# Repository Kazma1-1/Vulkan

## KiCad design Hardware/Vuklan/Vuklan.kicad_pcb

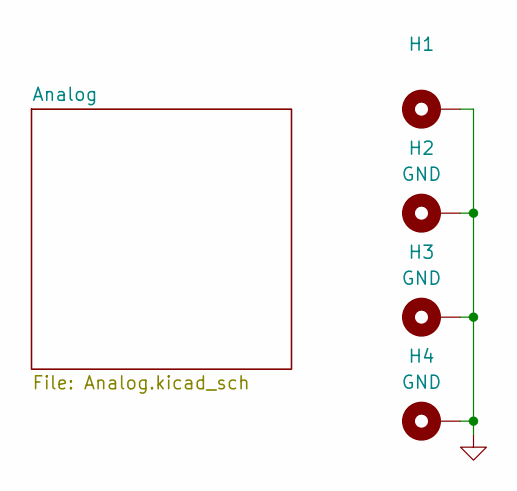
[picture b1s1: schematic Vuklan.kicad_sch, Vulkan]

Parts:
H1: (no value)
H2, H3, H4: GND

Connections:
GND: H1.1, H2.1, H3.1, H4.1; also elsewhere on the board

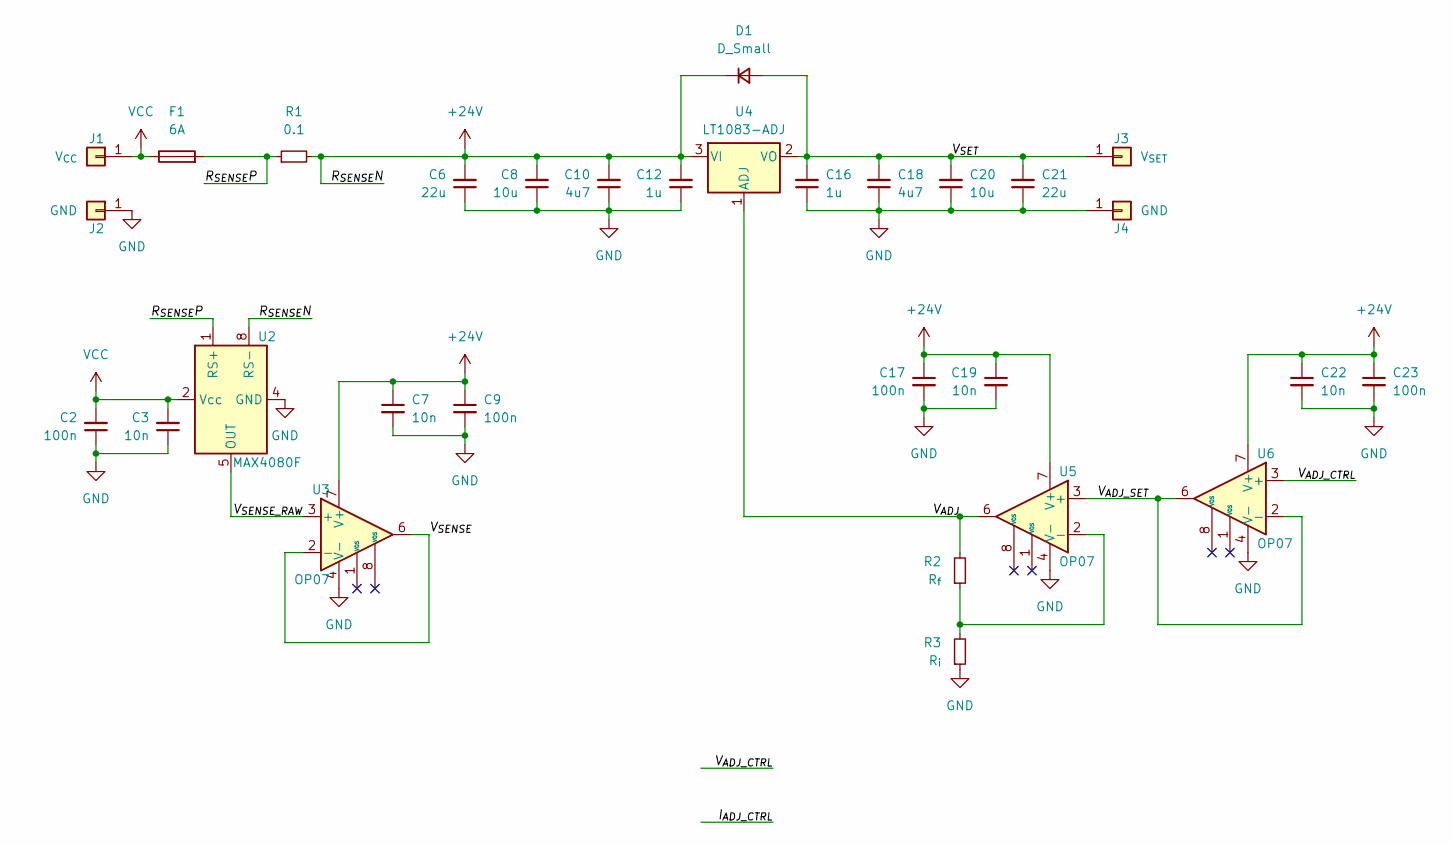
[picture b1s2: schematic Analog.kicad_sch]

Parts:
C2, C9, C17, C23: 100n
C3, C7, C19, C22: 10n
C6, C21: 22u
C8, C20: 10u
C10, C18: 4u7
C12, C16: 1u
D1: D_Small
F1: 6A
J1: V_{CC}
J2, J4: GND
J3: V_{SET}
R1: 0.1
R2: R_{f}
R3: R_{i}
U2: MAX4080F; SOIC-8_3.9x4.9mm_P1.27mm
U3, U5, U6: OP07
U4: LT1083-ADJ

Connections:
+24V: C6.2, C7.1, C8.2, C9.1, C10.2, C12.2, C17.1, C19.1, C22.1, C23.1, D1.1 (K), R1.2, U2.8 (RS-), U3.7 (V+), U4.3 (VI), U5.7 (V+), U6.7 (V+)
/Analog/R_{SENSE}P: F1.2, R1.1, U2.1 (RS+)
/Analog/V_{ADJ_CTRL}: U6.3 (+)
/Analog/V_{ADJ_SET}: U5.3 (+), U6.2 (-), U6.6
/Analog/V_{ADJ}: R2.2, U4.1 (ADJ), U5.6
/Analog/V_{SENSE_RAW}: U2.5 (OUT), U3.3 (+)
/Analog/V_{SENSE}: U3.2 (-), U3.6
/Analog/V_{SET}: C16.2, C18.2, C20.2, C21.2, D1.2 (A), J3.1, U4.2 (VO)
GND: C2.1, C3.1, C6.1, C7.2, C8.1, C9.2, C10.1, C12.1, C16.1, C17.2, C18.1, C19.2, C20.1, C21.1, C22.2, C23.2, J2.1, J4.1, R3.1, U2.4 (GND), U3.4 (V-), U5.4 (V-), U6.4 (V-); also elsewhere on the board
unnamed: R2.1, R3.2, U5.2 (-)
VCC: C2.2, C3.2, F1.1, J1.1, U2.2 (Vcc)

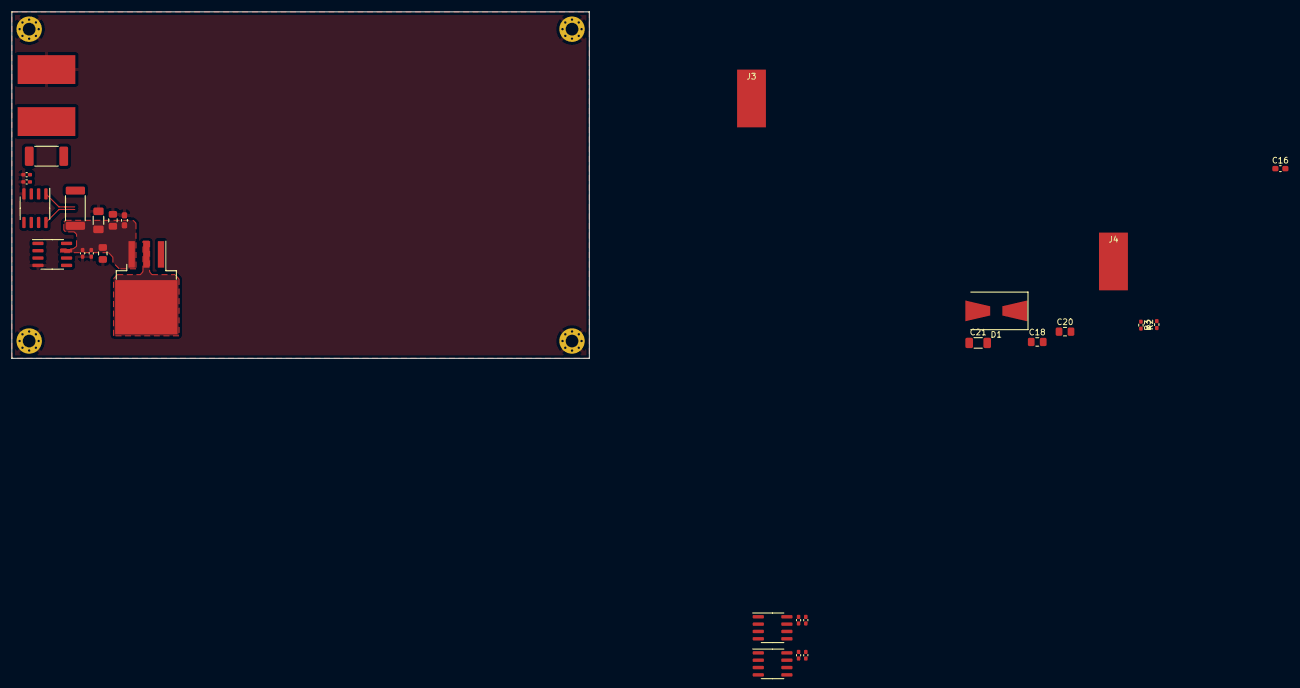
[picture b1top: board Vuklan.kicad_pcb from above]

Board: 4 copper layers, 100.0 x 60.0 mm, 34 parts (0 on the bottom side), 10 nets.

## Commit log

2022-05-16 Vulkan A LT Spice Simulation
2022-05-16 Rev 1A1 LT Spice Simulation, Simulation for current Limit.
2022-05-16 LT Spice Simulation, Voltage & Current Control.
